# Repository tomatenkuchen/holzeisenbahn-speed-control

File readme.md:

# Eisenbahn Project for my Son

This project supports building a wood train for my son. It should receive
a speed requirement via BLE, and return a current speed indication

- including a subscription.

The base is an ESP32C3 XIAO module for providing BLE functionality, and
PWM support for speed control.

Maybe we add a LED for lighting later on.

This code is mainly derived form the ble-nimble-gatt-server example in
[esp-idf](https://github.com/espressif/esp-idf/tree/master/examples/bluetooth/ble_get_started/nimble/NimBLE_GATT_Server)

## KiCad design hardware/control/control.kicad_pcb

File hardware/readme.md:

# train hardware

## Layout

This hardware layout is done using Kicad. You can download it for free [here](https://kicad.org).
The Idea is to put the engine and the battery on seperate wagons. This gives me more space and more
comfortably purchasable parts. So in the tradition of old steam engines, the motor is in front,
the charcoal heap (battery) on the rear wagon.

## BOM

The parts list (or bill of material - BOM) can be accessed here. If this shop isn't the right one for you,
use the one you prefer.

Otherwise, here's a list of the most important parts with a brief explaination.

| ID | Amount | Type|  Description |
| --- | --> | ---- | --- |
| IC1 | 1 | XIAO ESP32C6 board | microcontroller with bluetooth interface |
| IC2 | 1 | ST SPIN233 | low voltage motor voltage controller  |

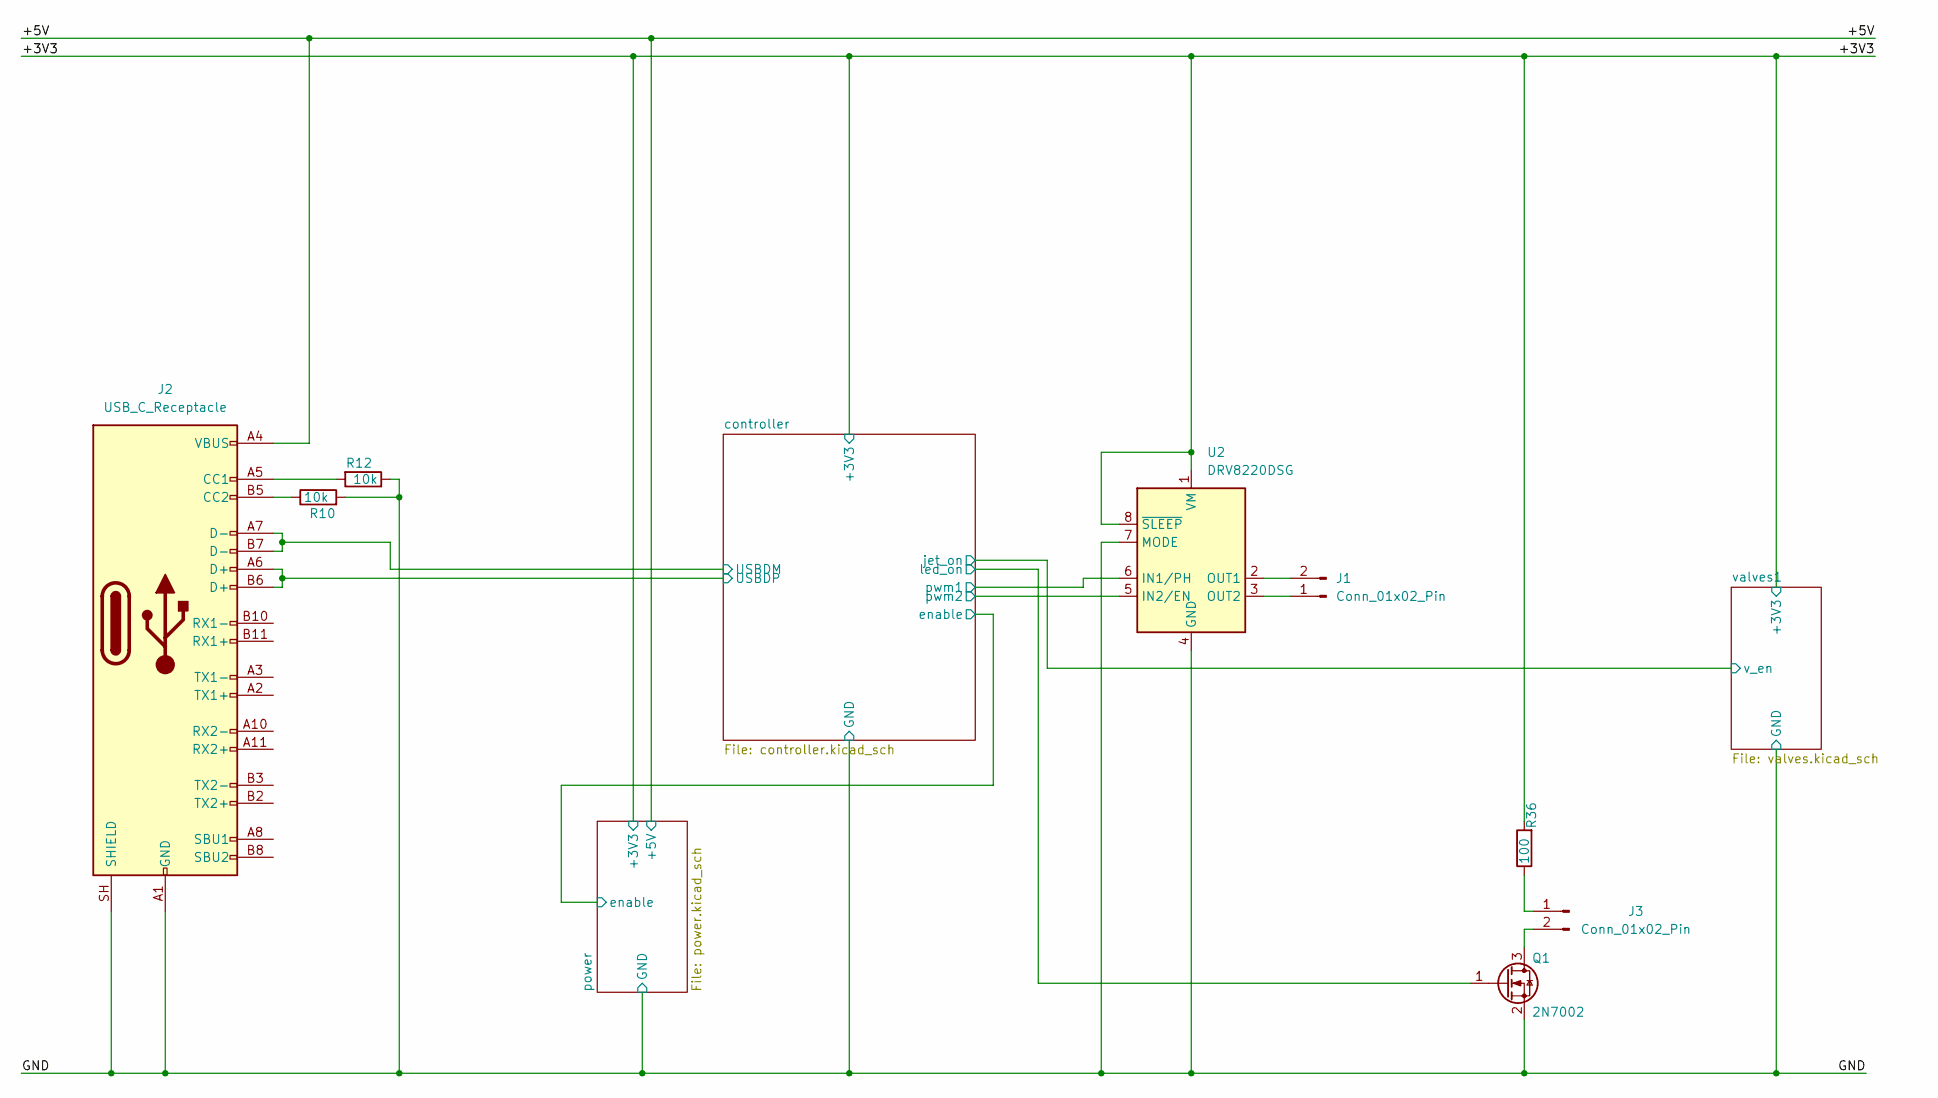
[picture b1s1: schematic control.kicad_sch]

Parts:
J1, J3: Conn_01x02_Pin; PinHeader_1x02_P1.27mm_Vertical
J2: USB_C_Receptacle; USB_C_Receptacle_GCT_USB4105-xx-A_16P_TopMnt_Horizontal
Q1: 2N7002; SOT-23
R10, R12: 10k; R_0603_1608Metric
R36: 100; R_0603_1608Metric
U2: DRV8220DSG; WSON-8-1EP_2x2mm_P0.5mm_EP0.9x1.6mm

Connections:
/+3V3: R36.2, U2.1 (VM), U2.8 (~SLEEP); also elsewhere on the board
/+5V: J2.A4 (VBUS), J2.A9 (VBUS), J2.B4 (VBUS), J2.B9 (VBUS); also elsewhere on the board
/GND: J2.A1 (GND), J2.A12 (GND), J2.B1 (GND), J2.B12 (GND), J2.SH (SHIELD), Q1.2 (S), R10.2, R12.1, U2.4 (GND), U2.7 (MODE), U2.9 (GND); also elsewhere on the board
/controller/USBDM: J2.A7 (D-), J2.B7 (D-); also elsewhere on the board
/controller/USBDP: J2.A6 (D+), J2.B6 (D+); also elsewhere on the board
/controller/led_on: Q1.1 (G); also elsewhere on the board
/controller/pwm1: U2.6 (IN1/PH); also elsewhere on the board
/controller/pwm2: U2.5 (IN2/EN); also elsewhere on the board
unnamed: J1.1, U2.3 (OUT2)
unnamed: J1.2, U2.2 (OUT1)
unnamed: J2.A5 (CC1), R12.2
unnamed: J2.B5 (CC2), R10.1
unnamed: J3.1, R36.1
unnamed: J3.2, Q1.3 (D)

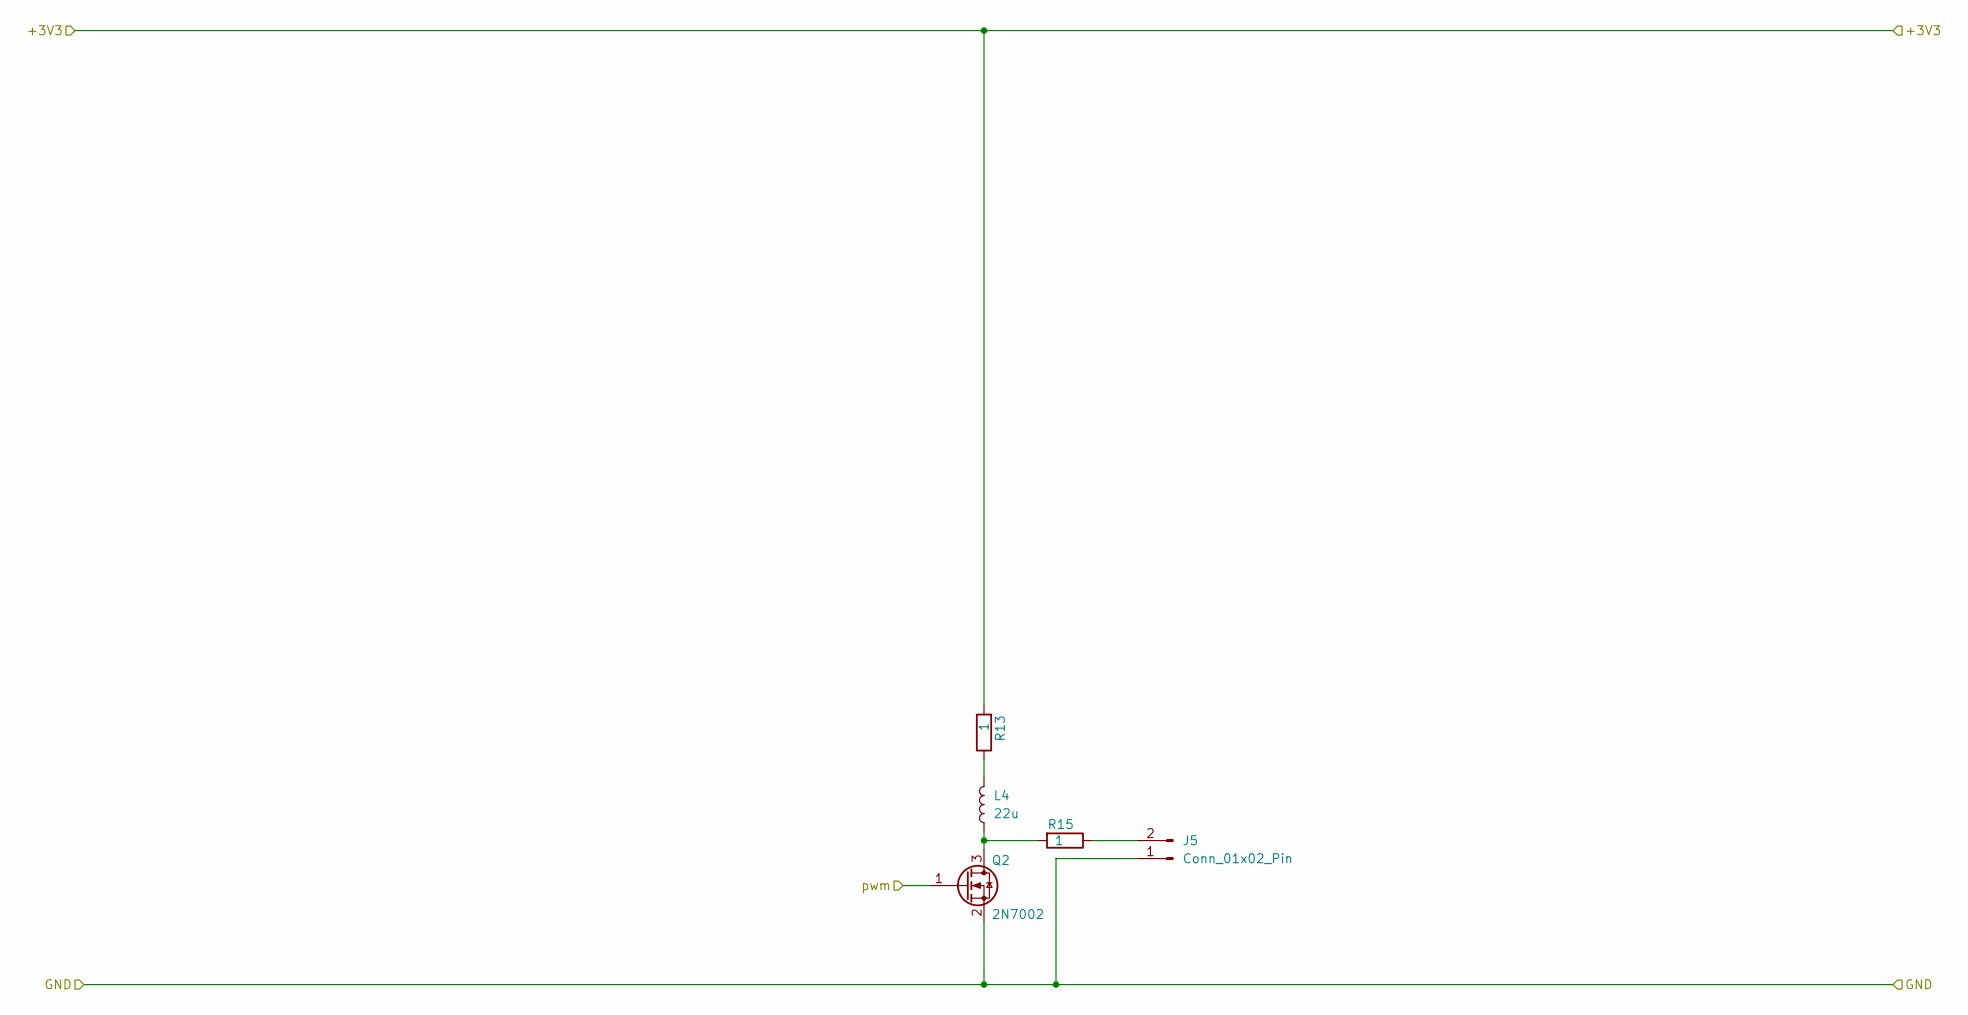
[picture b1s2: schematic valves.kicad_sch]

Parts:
J5: Conn_01x02_Pin; PinHeader_1x02_P1.27mm_Vertical
L4: 22u; L_Changjiang_FTC303020D
Q2: 2N7002; SOT-23
R13, R15: 1; R_0603_1608Metric

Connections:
/+3V3: R13.2; also elsewhere on the board
/GND: J5.1, Q2.2 (S); also elsewhere on the board
/valves1/pwm: Q2.1 (G)
unnamed: J5.2, R15.1
unnamed: L4.2, R13.1
unnamed: L4.1, Q2.3 (D), R15.2

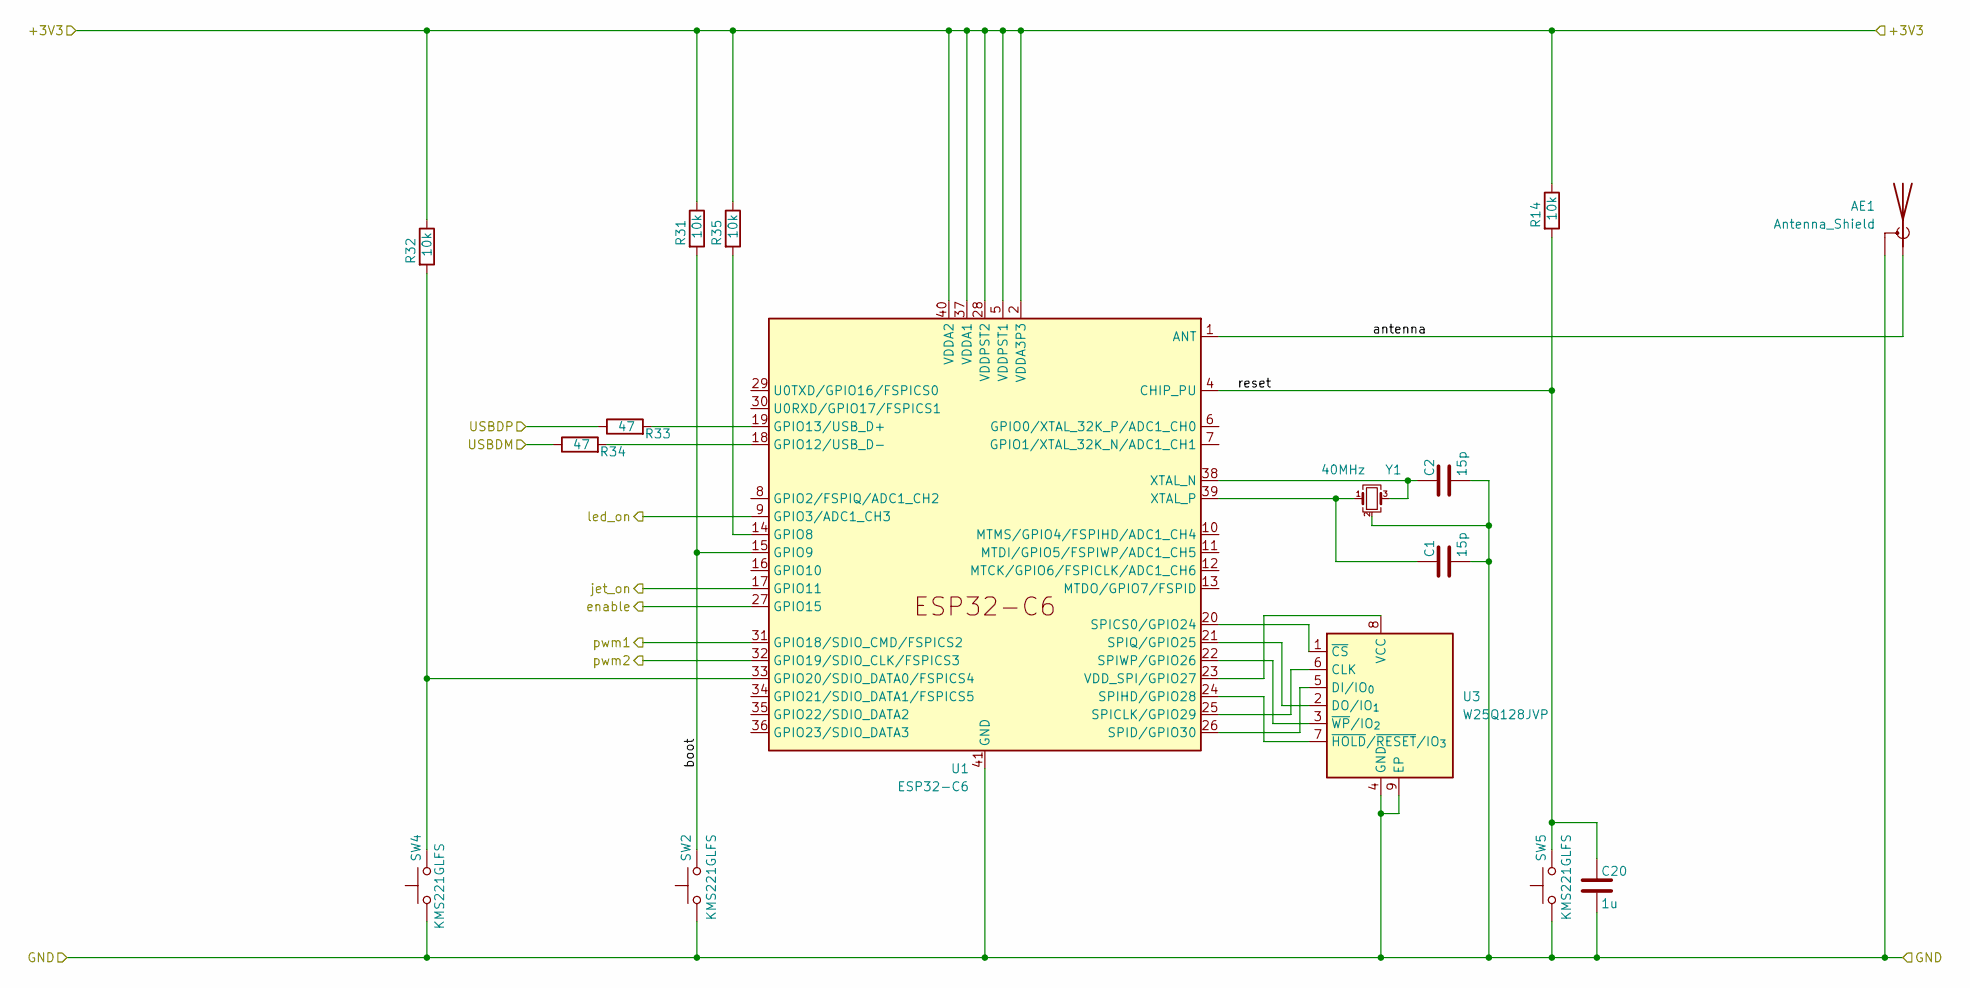
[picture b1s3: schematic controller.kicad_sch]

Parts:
AE1: Antenna_Shield; Texas_SWRA117D_2.4GHz_Left
C1, C2: 15p; C_0603_1608Metric
C20: 1u; C_0603_1608Metric
R14, R31, R32, R35: 10k; R_0603_1608Metric
R33, R34: 47; R_0603_1608Metric
SW2, SW5: KMS221GLFS; SW_SPST_TS-1088-xR020
SW4: KMS221GLFS; SW_Push_1P1T_XKB_TS-1187A
U1: ESP32-C6; QFN-40-1EP_5x5mm_P0.4mm_EP3.6x3.6mm
U3: W25Q128JVP; WSON-8-1EP_6x5mm_P1.27mm_EP3.4x4.3mm
Y1: 40MHz; Crystal_SMD_3225-4Pin_3.2x2.5mm

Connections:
/+3V3: R14.1, R31.1, R32.1, R35.1, U1.2 (VDDA3P3), U1.3 (VDDA3P3), U1.5 (VDDPST1), U1.28 (VDDPST2), U1.37 (VDDA1), U1.40 (VDDA2); also elsewhere on the board
/GND: AE1.2 (Shield), C1.2, C2.2, C20.2, SW2.1, SW4.1, SW5.1, U1.41 (GND), U3.4 (GND), U3.9 (EP), Y1.2 (G), Y1.4 (G); also elsewhere on the board
/controller/USBDM: R34.1; also elsewhere on the board
/controller/USBDP: R33.1; also elsewhere on the board
/controller/antenna: AE1.1 (A), U1.1 (ANT)
/controller/boot: R31.2, SW2.2, U1.15 (GPIO9)
/controller/enable: U1.27 (GPIO15); also elsewhere on the board
/controller/jet_on: U1.17 (GPIO11)
/controller/led_on: U1.9 (GPIO3/ADC1_CH3); also elsewhere on the board
/controller/pwm1: U1.31 (GPIO18/SDIO_CMD/FSPICS2); also elsewhere on the board
/controller/pwm2: U1.32 (GPIO19/SDIO_CLK/FSPICS3); also elsewhere on the board
/controller/reset: C20.1, R14.2, SW5.2, U1.4 (CHIP_PU)
unnamed: R35.2, U1.14 (GPIO8)
unnamed: R34.2, U1.18 (GPIO12/USB_D-)
unnamed: R33.2, U1.19 (GPIO13/USB_D+)
unnamed: R32.2, SW4.2, U1.33 (GPIO20/SDIO_DATA0/FSPICS4)
unnamed: U1.25 (SPICLK/GPIO29), U3.6 (CLK)
unnamed: U1.20 (SPICS0/GPIO24), U3.1 (~CS)
unnamed: U1.26 (SPID/GPIO30), U3.5 (DI/IO_{0})
unnamed: U1.24 (SPIHD/GPIO28), U3.7 (~HOLD/~RESET/IO_{3})
unnamed: U1.21 (SPIQ/GPIO25), U3.2 (DO/IO_{1})
unnamed: U1.22 (SPIWP/GPIO26), U3.3 (~WP/IO_{2})
unnamed: U1.23 (VDD_SPI/GPIO27), U3.8 (VCC)
unnamed: C2.1, U1.38 (XTAL_N), Y1.3
unnamed: C1.1, U1.39 (XTAL_P), Y1.1

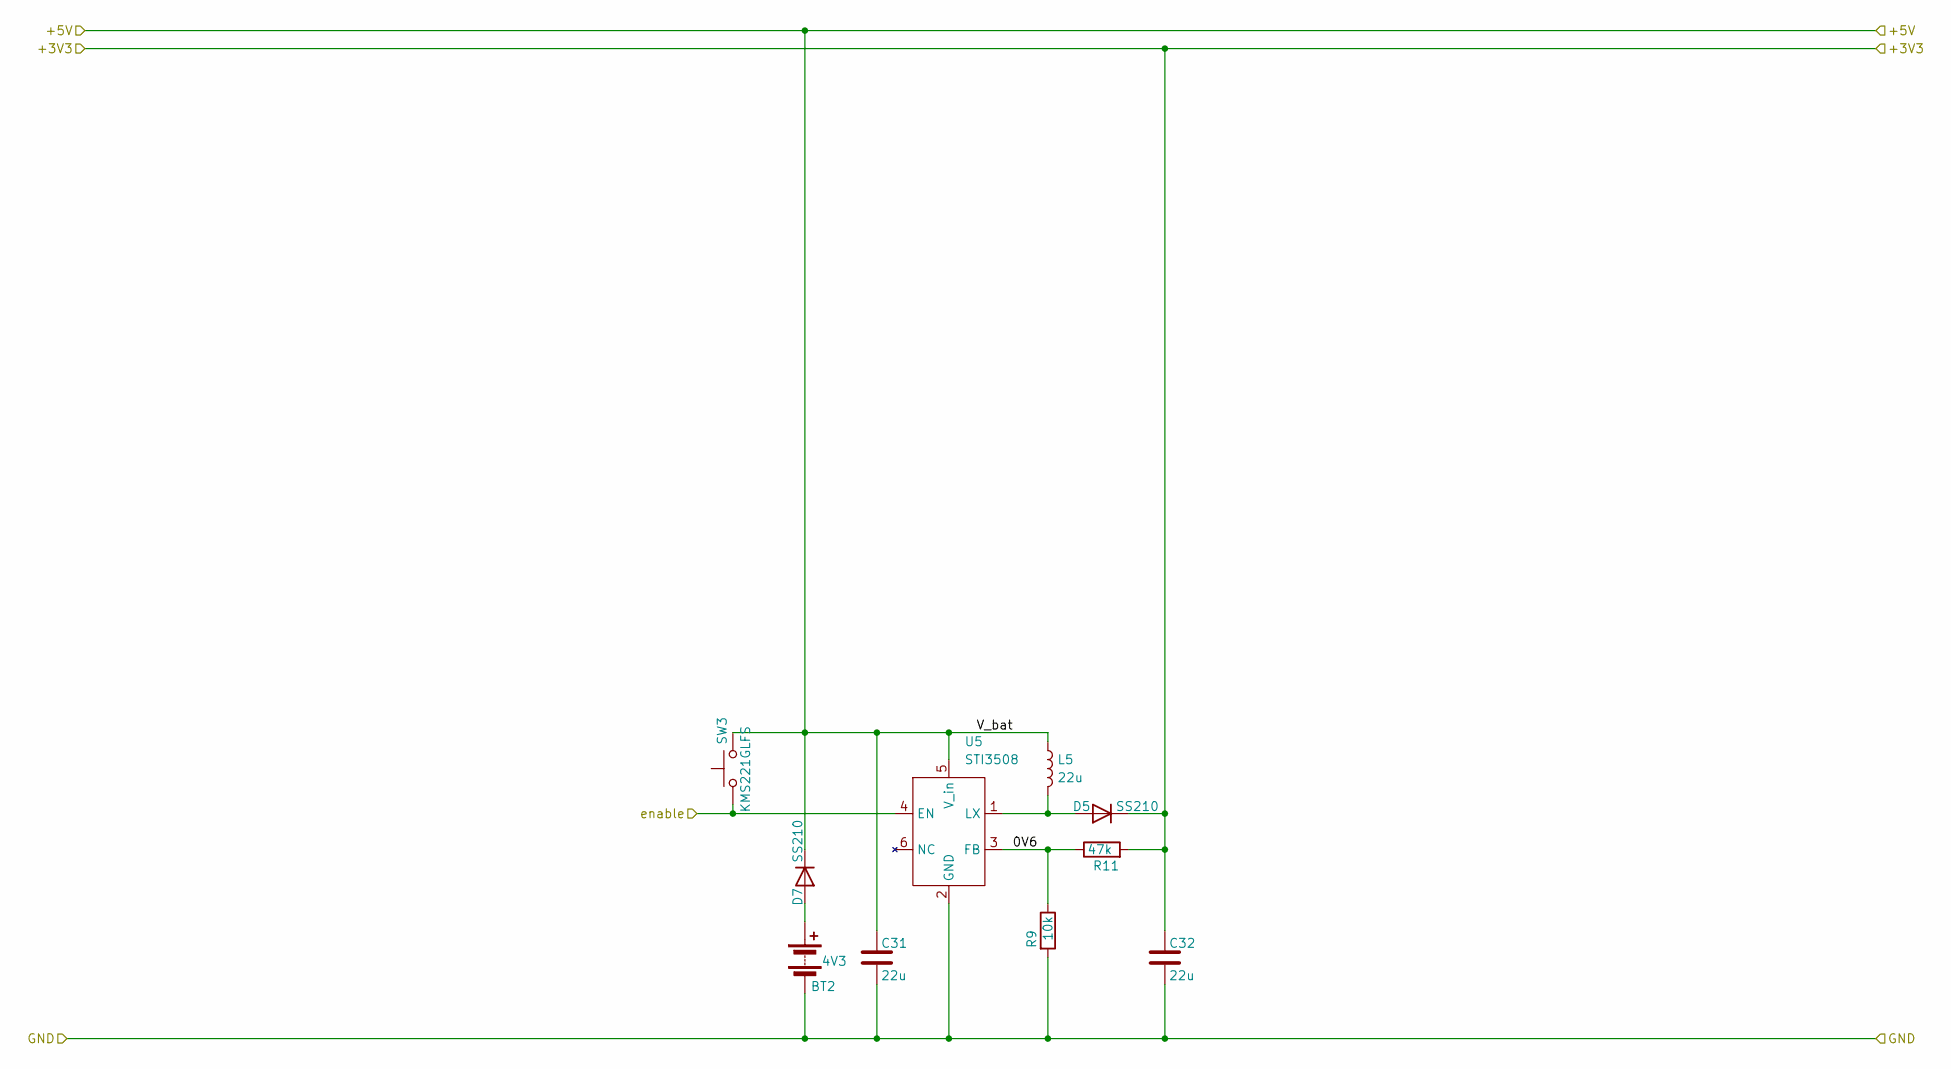
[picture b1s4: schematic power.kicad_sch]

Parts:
BT2: 4V3; PinHeader_1x02_P1.27mm_Vertical
C31, C32: 22u; C_1206_3216Metric
D5, D7: SS210; D_SMA
L5: 22u; L_Changjiang_FTC303020D
R9: 10k; R_0603_1608Metric
R11: 47k; R_0603_1608Metric
SW3: KMS221GLFS; SW_Push_1P1T_XKB_TS-1187A
U5: STI3508; SOT-23-6

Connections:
/+3V3: C32.1, D5.1 (K), R11.2; also elsewhere on the board
/+5V: C31.1, D7.1 (K), L5.1, SW3.2, U5.5 (V_in); also elsewhere on the board
/GND: BT2.2 (-), C31.2, C32.2, R9.2, U5.2 (GND); also elsewhere on the board
/controller/enable: SW3.1, U5.4 (EN); also elsewhere on the board
/power/0V6: R9.1, R11.1, U5.3 (FB)
unnamed: BT2.1 (+), D7.2 (A)
unnamed: D5.2 (A), L5.2, U5.1 (LX)

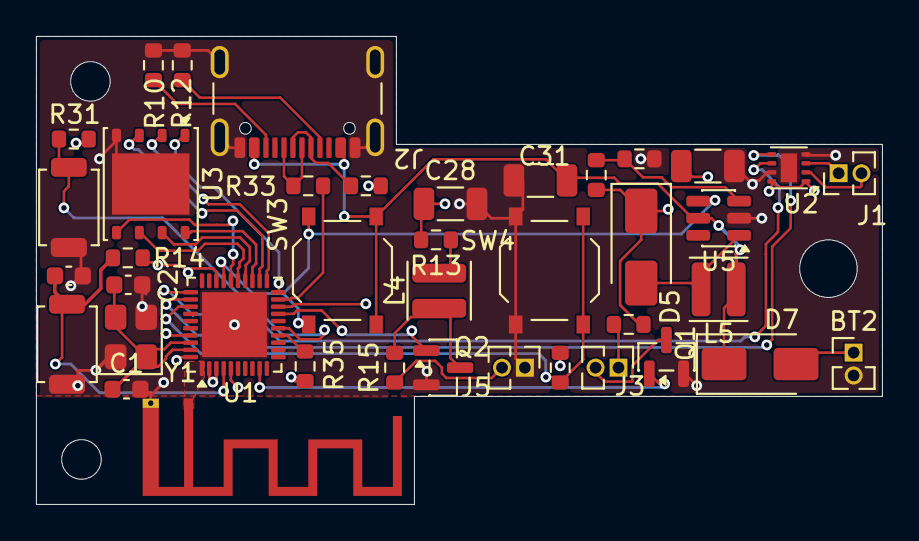
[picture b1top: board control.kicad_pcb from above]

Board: 4 copper layers, 47.0 x 26.0 mm, 40 parts (0 on the bottom side), 37 nets.

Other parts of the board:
C28: 22u; C_1206_3216Metric

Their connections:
/+3V3: C28.1; also elsewhere on the board
/GND: C28.2; also elsewhere on the board

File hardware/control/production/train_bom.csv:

Designator,Footprint,Quantity,Value,LCSC Part #
AE1,Texas_SWRA117D_2.4GHz_Left,1,Antenna_Shield,
BT2,PinHeader_1x02_P1.27mm_Vertical,1,4V3,
"C1, C2",603,2,15p,C1644
C20,603,1,1u,C15849
"C28, C31, C32",1206,3,22u,C12891
"D5, D7",D_SMA,2,SS210,C14996
"J1, J3, J5",PinHeader_1x02_P1.27mm_Vertical,3,Conn_01x02_Pin,
J2,USB_C_Receptacle_GCT_USB4105-xx-A_16P_TopMnt_Horizontal,1,USB_C_Receptacle,C2927038
"L3, L4",L_Wuerth_MAPI-4030,2,22u,C843299
"Q1, Q2",SOT-23,2,2N7002,C8545
"R10, R12, R14, R31, R32, R35, R9",603,7,10k,C25804
R11,603,1,47k,C25819
"R13, R15",603,2,1,C22936
"R33, R34",603,2,47,C23182
R36,603,1,100,C22775
"SW2, SW5",SW_SPST_TS-1088-xR020,2,KMS221GLFS,C720477
"SW3, SW4",SW_Push_1P1T_XKB_TS-1187A,2,KMS221GLFS,C318884
U1,QFN-40-1EP_5x5mm_P0.4mm_EP3.6x3.6mm,1,ESP32-C6,C5364646
U2,WSON-8-1EP_2x2mm_P0.5mm_EP0.9x1.6mm,1,DRV8220DSG,C3681269
U3,WSON-8-1EP_6x5mm_P1.27mm_EP3.4x4.3mm,1,W25Q128JVP,C190862
U5,SOT-23-6,1,STI3508,C708881
Y1,Crystal_SMD_3225-4Pin_3.2x2.5mm,1,40MHz,C9010

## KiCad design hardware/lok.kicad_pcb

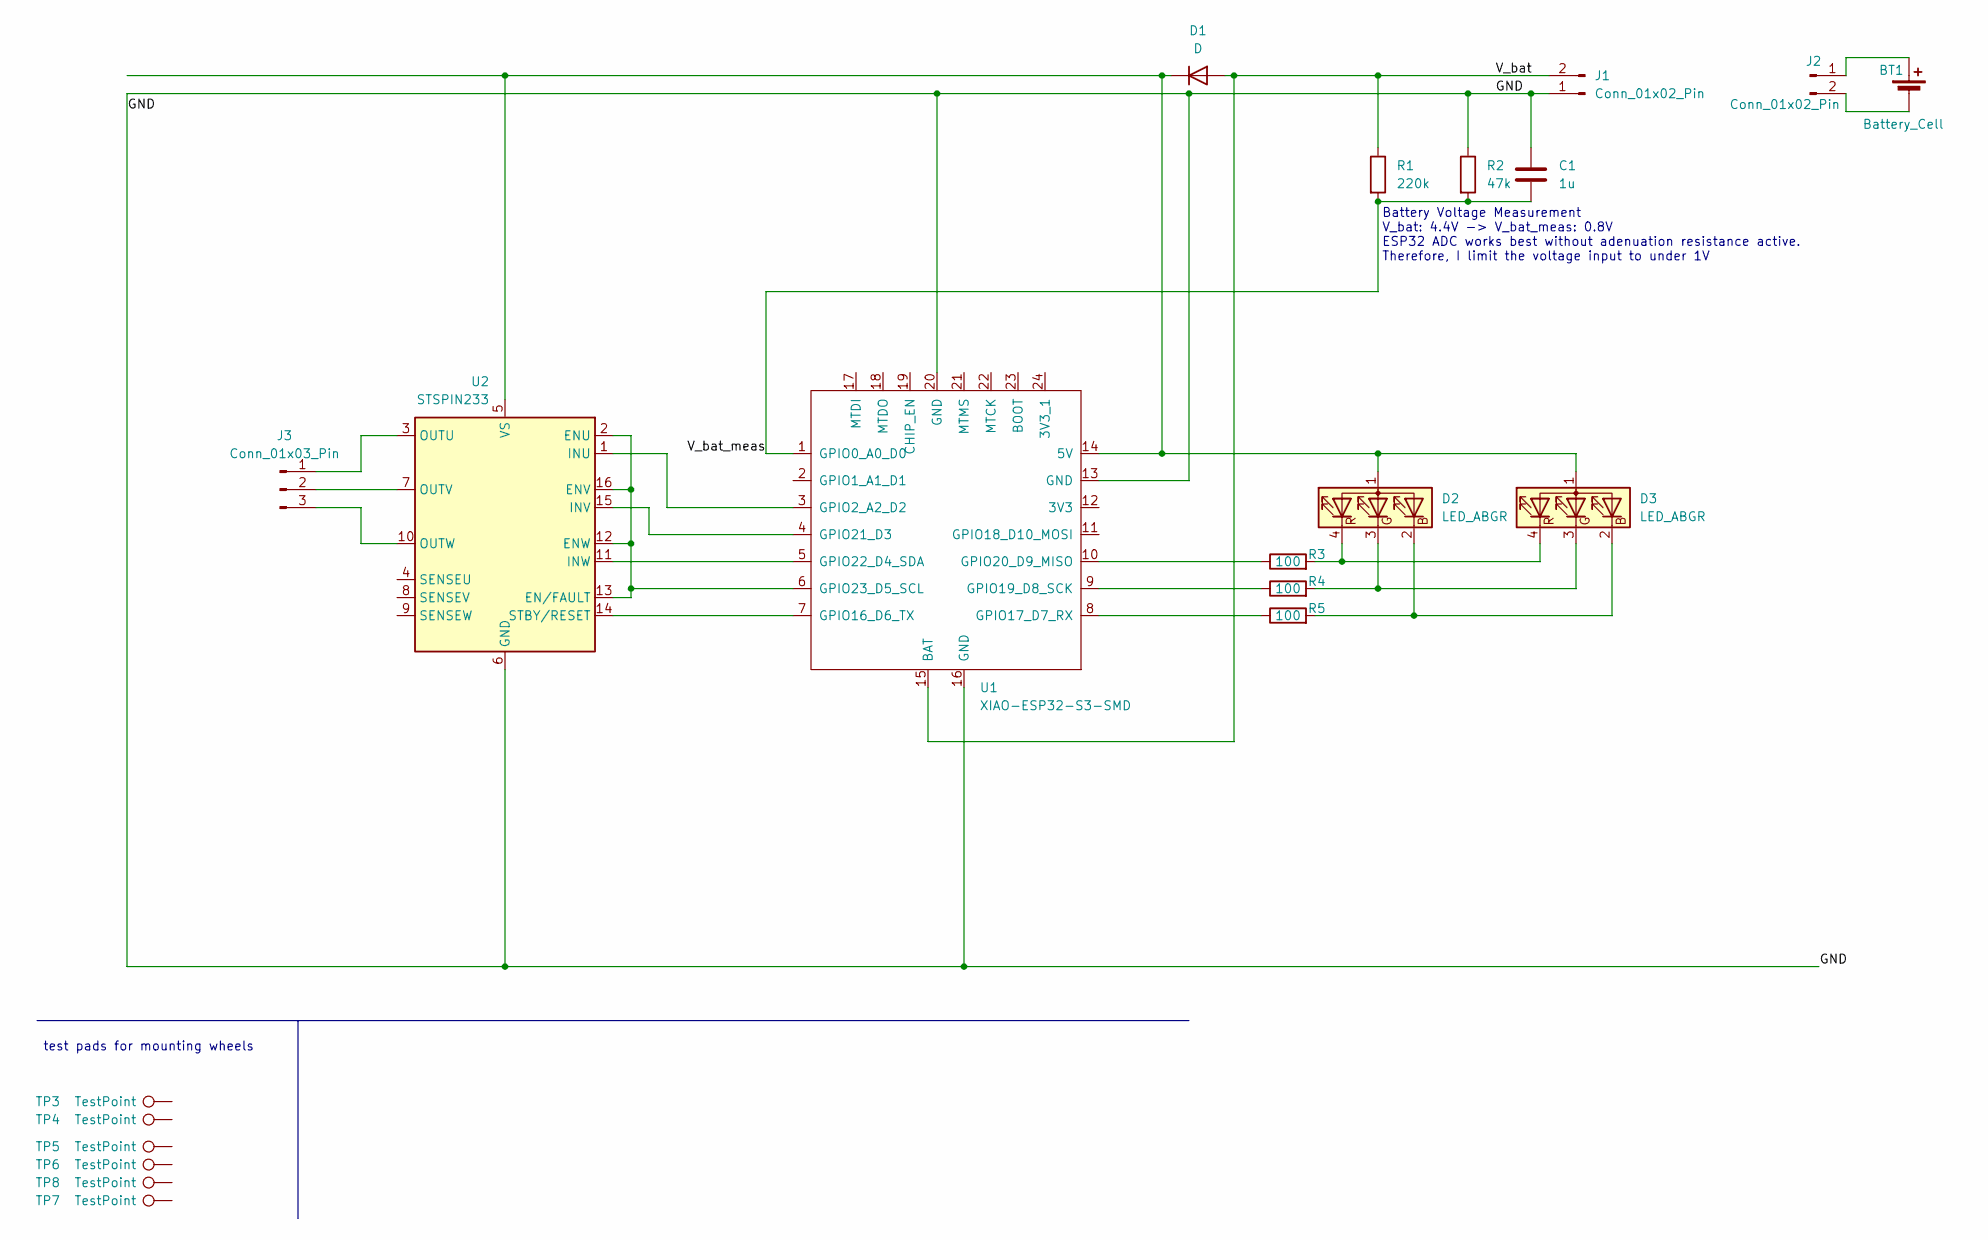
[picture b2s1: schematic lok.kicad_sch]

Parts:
BT1: Battery_Cell; BatteryHolder_Keystone_1042_1x18650
C1: 1u; C_0603_1608Metric
D1: D; D_SOD-123F
D2, D3: LED_ABGR; LED_Kingbright_APFA3010_3x1.5mm_Horizontal
J1, J2: Conn_01x02_Pin; PinHeader_1x02_P2.54mm_Vertical
J3: Conn_01x03_Pin; PinHeader_1x03_P2.54mm_Vertical
R1: 220k; R_0603_1608Metric
R2: 47k; R_0603_1608Metric
R3, R4, R5: 100; R_0603_1608Metric
TP3, TP4, TP5, TP6, TP7, TP8: TestPoint; TestPoint_Keystone_5019_Miniature
U1: XIAO-ESP32-S3-SMD; MCU_Seeed_ESP32C3
U2: STSPIN233; VQFN-16-1EP_3x3mm_P0.5mm_EP1.8x1.8mm

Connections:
/GND: C1.1, J1.1, R2.1, U1.13 (GND), U1.16 (GND), U1.20 (GND), U2.6 (GND), U2.17 (GND)
/V_bat: D1.2 (A), J1.2, R1.1, U1.15 (BAT)
/V_bat_meas: C1.2, R1.2, R2.2, U1.1 (GPIO0_A0_D0)
unnamed: BT1.1 (+), J2.1
unnamed: BT1.2 (-), J2.2
unnamed: D1.1 (K), D2.1 (A), D3.1 (A), U1.14 (5V), U2.5 (VS)
unnamed: D2.2 (BK), D3.2 (BK), R5.2
unnamed: D2.3 (GK), D3.3 (GK), R4.2
unnamed: D2.4 (RK), D3.4 (RK), R3.2
unnamed: J3.1, U2.3 (OUTU)
unnamed: J3.2, U2.7 (OUTV)
unnamed: J3.3, U2.10 (OUTW)
unnamed: U1.3 (GPIO2_A2_D2), U2.1 (INU)
unnamed: U1.7 (GPIO16_D6_TX), U2.14 (STBY/RESET)
unnamed: R5.1, U1.8 (GPIO17_D7_RX)
unnamed: R4.1, U1.9 (GPIO19_D8_SCK)
unnamed: R3.1, U1.10 (GPIO20_D9_MISO)
unnamed: U1.4 (GPIO21_D3), U2.15 (INV)
unnamed: U1.5 (GPIO22_D4_SDA), U2.11 (INW)
unnamed: U1.6 (GPIO23_D5_SCL), U2.2 (ENU), U2.12 (ENW), U2.13 (EN/FAULT), U2.16 (ENV)

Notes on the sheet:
test pads for mounting wheels
Battery Voltage Measurement V_bat: 4.4V -> V_bat_meas: 0.8V ESP32 ADC works best without adenuation resistance active. Therefore, I limit the voltage input to under 1V

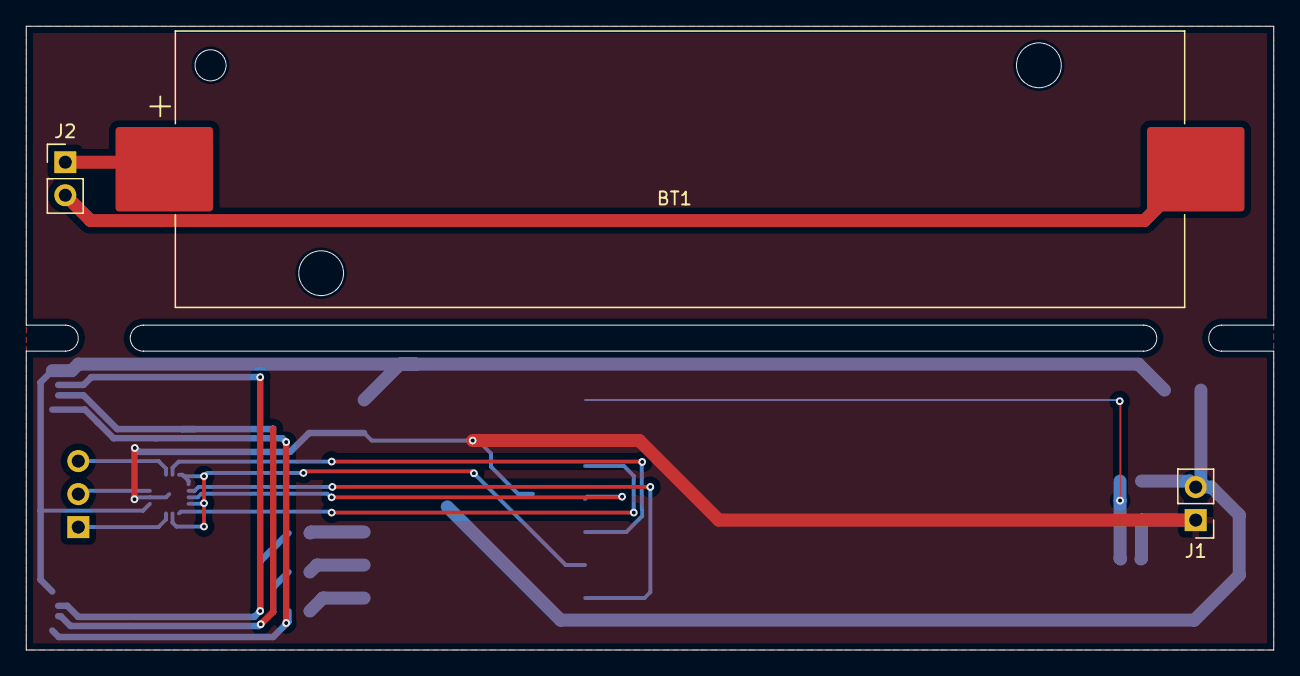
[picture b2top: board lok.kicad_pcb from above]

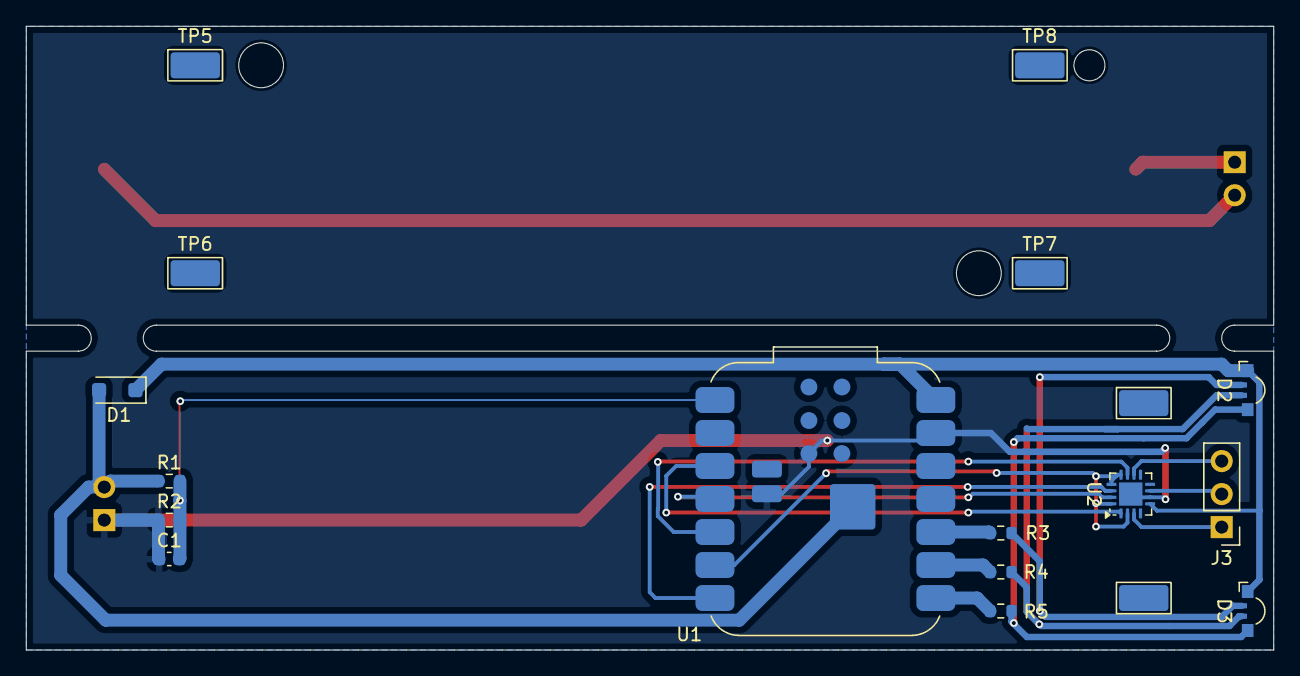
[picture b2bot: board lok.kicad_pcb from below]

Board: 2 copper layers, 96.0 x 48.0 mm, 21 parts (18 on the bottom side), 20 nets.

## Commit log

2024-11-24 root
2024-11-24 bugfix
2024-11-29 - changed folder name - packed led driver to class
2024-11-29 added ble class
2024-11-29 added deepsleep mode to safe battery life
2024-12-24 updated to project with ble part included
2024-12-24 moved readme to root
2024-12-25 - provisioned dummy speed measurement function for the project to link - bugfix pid: initialization order - compiles!
2024-12-25 - changed error reporting of gap handler and advertizer to c++ exceptions
2024-12-25 groomed up gatt
2024-12-25 renamed gatt_svc to gatt
2024-12-25 introduced namespaces to gatt and gap to make things more clear of their origin
2024-12-26 replaced example readme with project specific
2024-12-26 tried to ease reading by substituting macros with structs
2024-12-27 - changed server to service in variable and function names to comply to bluetooth lingo - created service and characteristic structs to cram all those loose variables together. still hard to follow t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
2024-12-27 gap service: changed char array to string
2024-12-27 updated some names in gap service
2024-12-27 some logging simplifications on gap
2024-12-27 - changed name to tomato-ble - changed uuid of led to automation io uuid16. somehow the requested datatype is no longer visible as bool
2024-12-29 tried to make ble class as generic as possible
2025-01-01 - created nimble class for proper initialization in ble class - formatted license text to a markdown file
2025-01-01 -moved license text to root - license.md markdown correction
2025-01-01 license text correction
2025-01-01 license markdown amends
2025-01-01 some ble class adaptations
2025-01-13 stuff
2025-05-03 - changed target to esp32c6 - set up esp example once more to avoid ble issues
2025-05-03 updated licese and readme
2025-05-04 simplified gatt
2025-05-05 substituted common.hpp
2025-05-05 - removed common.hpp - tried to implement gap class. integration into ble class not yet possible
2025-05-06 added speed control module
2025-05-08 - groomed up gap class
2025-05-08 integrated gap into ble class
2025-05-08 added gap callback to start advertizing function arguments
2025-05-12 some progress on gatt/gap
2025-05-22 added pid
2025-05-22 added datasheets and xiao schematics
2025-05-22 renamed gatt module to gatt.xpp
2025-05-23 resolved some include errors
2025-05-24 added lambda to gap for callback
2025-05-24 solved the event handler issue in gap by using a lambda directly
2025-05-25 added rgb leds
2025-05-25 chores
2025-05-29 added readme to hardware
2025-05-29 added battery holder
2025-06-01 resolved gap service back to plain c calls because i couln't solve the callback via lambda issue...
2025-06-03 tried to simplify gatt
2025-06-08 updated gatt
2025-06-08 new schematic
2025-06-15 some updates on gatt
2025-06-15 packed all ble stuff into ble module since gap and gatt were intertwined anyway too much
2025-06-15 less mess
2025-06-16 tried to stuff everything into ble class
2025-06-16 moved ble enums
2025-06-19 removed some log only events to make program more slender
2025-06-22 bugfixes
2025-06-22 compiles now, but doesn't work
2025-06-22 removed heart rate stuff
2025-06-22 try to fix host sync error. no success
2025-06-23 added ble sync
2025-06-24 solved gap init error
2025-06-25 added second led to try
2025-06-25 - added some more log statements - moved heart beat task to ble task. it's added for now to have ble object not destroyed at the end of the task
2025-06-25 bugfix led2
2025-06-26 added led controller
2025-06-26 added sample program from example for rgb leds
2025-06-26 added ledc driver as dependency
2025-06-26 make led with gamma correction a class
2025-06-27 exchanged led class with ledc controller hw implementation
2025-06-27 simplified gamma formula
2025-06-27 finally realized that templates aren't suppoed to be in a source file...|
2025-06-27 removed gamma factor because it complicates things enormously
2025-06-28 moved hardware stuff to lok folder
2025-06-28 more move
2025-06-29 added inverter module
2025-06-29 added led config to lok class
2025-06-29 added tacho module
2025-06-29 moved some hardware init stuff to the inverter and tacho class. i want it more to be like a bsp
2025-06-29 more std::chrono in tacho:
2025-07-06 more bugfixes
2025-07-06 some more bugfixes
2025-07-08 added callbacks
2025-07-08 added adc config to inverter
2025-07-13 adc progress
2025-07-13 compiles and links
2025-07-14 - added constructor initializer pack never - added callback to speed pin tacho
2025-07-26 changed build type to Og
2025-07-26 updated to esp32c6 target
2025-07-27 moved led config to lok
2025-07-27 reintroduce measurement to speed control
2025-07-27 added some logs
2025-07-27 - moved tacho init to the bottom to avoid interference with pin state
2025-07-27 more stuff
2025-08-09 moved gitignore
2025-11-16 updated ble
2026-06-11 first pitch
2026-06-13 done routing
2026-06-13 changed switches due to shortage
2026-06-13 updated production
2026-06-13 final
2026-06-15 changed inductor for jlc compliance
2026-06-15 updated bom
